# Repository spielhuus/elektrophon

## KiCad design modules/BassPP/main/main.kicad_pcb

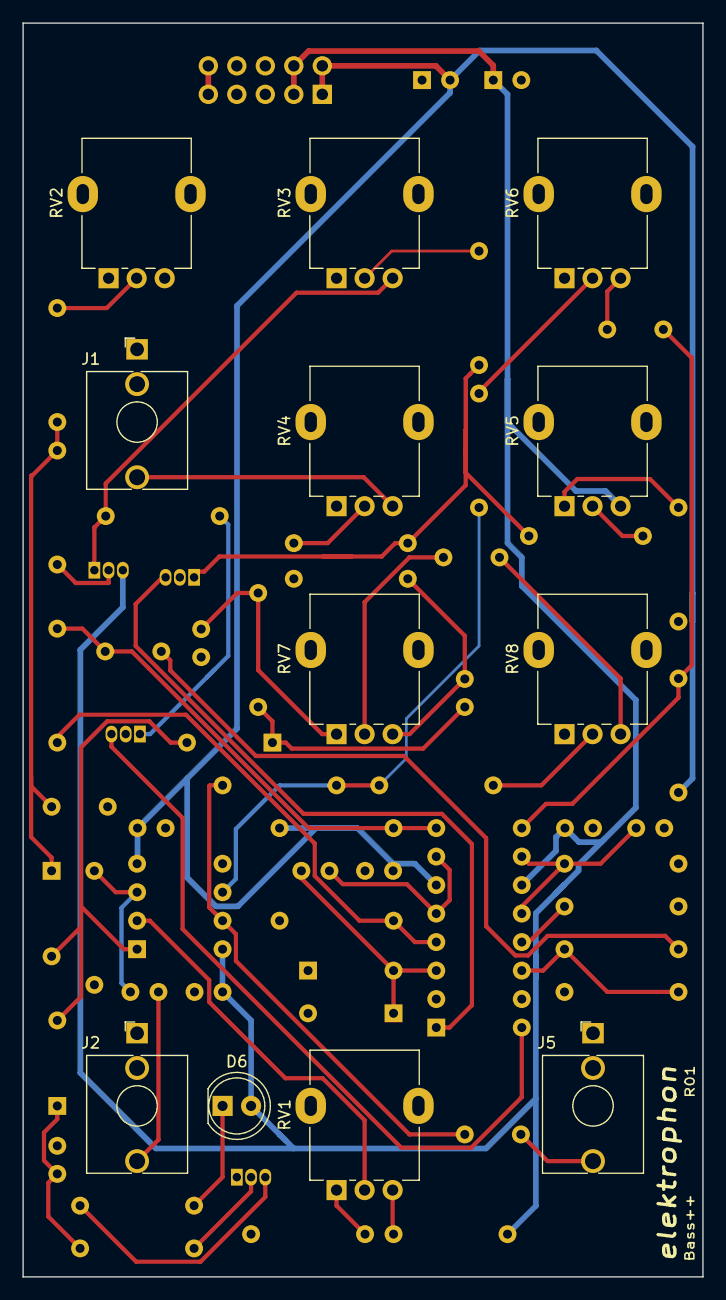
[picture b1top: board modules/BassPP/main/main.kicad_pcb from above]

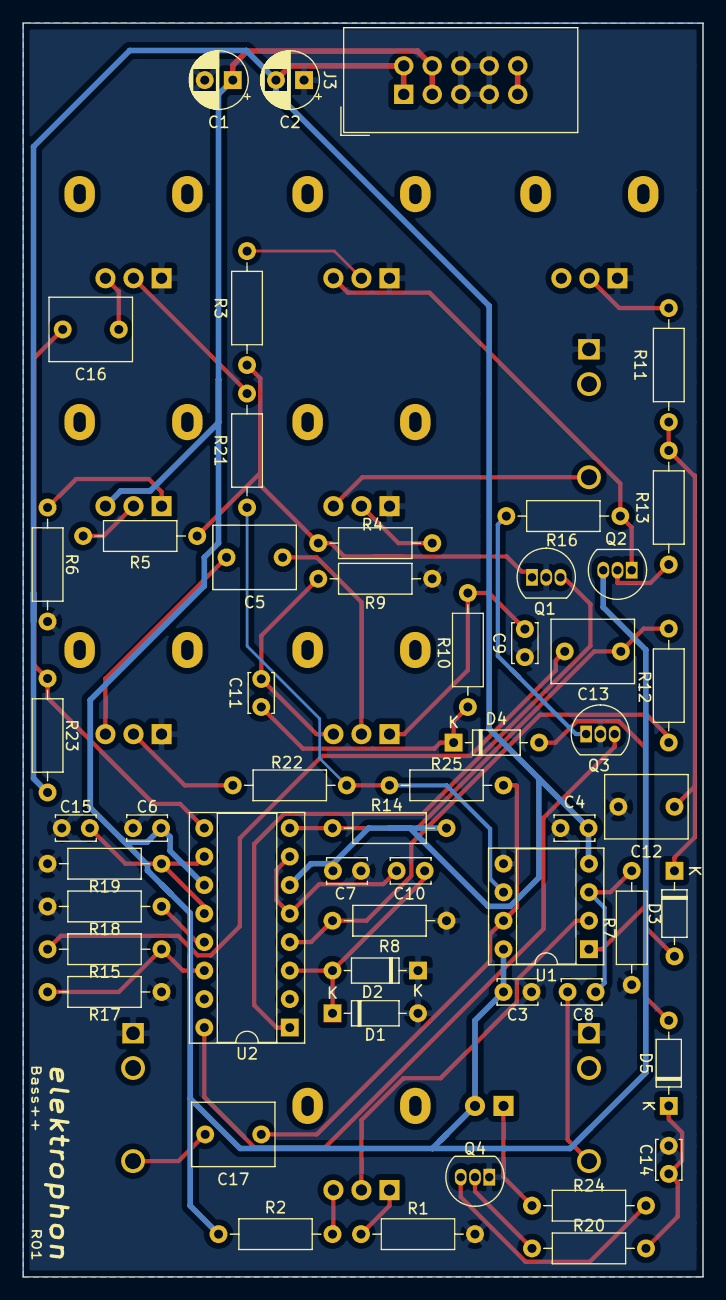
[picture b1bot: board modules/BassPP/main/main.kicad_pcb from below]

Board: 2 copper layers, 60.6 x 111.8 mm, 66 parts (54 on the bottom side), 47 nets.

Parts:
C1, C2: 10u; CP_Radial_D5.0mm_P2.50mm
C3, C4, C6, C7, C9, C11: 0.1u; C_Disc_D3.4mm_W2.1mm_P2.50mm
C5, C12, C13, C16, C17: 2u2; C_Rect_L7.2mm_W5.5mm_P5.00mm_FKS2_FKP2_MKS2_MKP2
C8: 1n; C_Disc_D3.4mm_W2.1mm_P2.50mm
C10, C14, C15: 10n; C_Disc_D3.4mm_W2.1mm_P2.50mm
D1, D2, D3, D4, D5: 1N4148; D_DO-35_SOD27_P7.62mm_Horizontal
D6: LED; LED_D5.0mm
J1, J5: CV; Jack_3.5mm_QingPu_WQP-PJ398SM_Vertical_CircularHoles
J2: Trigger; Jack_3.5mm_QingPu_WQP-PJ398SM_Vertical_CircularHoles
J3: IDC Header; IDC-Header_2x05_P2.54mm_Vertical
Q1, Q3: 2N3906; TO-92_Inline
Q2, Q4: 2N3904; TO-92_Inline
R1: 100; R_Axial_DIN0207_L6.3mm_D2.5mm_P10.16mm_Horizontal
R2, R12, R16: 20k; R_Axial_DIN0207_L6.3mm_D2.5mm_P10.16mm_Horizontal
R3, R15, R21, R22, R25: 100k; R_Axial_DIN0207_L6.3mm_D2.5mm_P10.16mm_Horizontal
R4, R19: 56k; R_Axial_DIN0207_L6.3mm_D2.5mm_P10.16mm_Horizontal
R5: 27k; R_Axial_DIN0207_L6.3mm_D2.5mm_P10.16mm_Horizontal
R6: 3k3; R_Axial_DIN0207_L6.3mm_D2.5mm_P10.16mm_Horizontal
R7: 1M; R_Axial_DIN0207_L6.3mm_D2.5mm_P10.16mm_Horizontal
R8, R9: 2k; R_Axial_DIN0207_L6.3mm_D2.5mm_P10.16mm_Horizontal
R10, R13, R23: 10k; R_Axial_DIN0207_L6.3mm_D2.5mm_P10.16mm_Horizontal
R11: 1k; R_Axial_DIN0207_L6.3mm_D2.5mm_P10.16mm_Horizontal
R14: 5k1; R_Axial_DIN0207_L6.3mm_D2.5mm_P10.16mm_Horizontal
R17, R18: 220; R_Axial_DIN0207_L6.3mm_D2.5mm_P10.16mm_Horizontal
R20: 220k; R_Axial_DIN0207_L6.3mm_D2.5mm_P10.16mm_Horizontal
R24: 1.5k; R_Axial_DIN0207_L6.3mm_D2.5mm_P10.16mm_Horizontal
RV1, RV3, RV7: 10k; Potentiometer_Alpha_RD901F-40-00D_Single_Vertical
RV2: 500k; Potentiometer_Alpha_RD901F-40-00D_Single_Vertical
RV4, RV5, RV6, RV8: 100k; Potentiometer_Alpha_RD901F-40-00D_Single_Vertical
U1: TL072; DIP-8_W7.62mm_Socket
U2: LM13700; DIP-16_W7.62mm_Socket

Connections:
+5V: J3.9, J3.10
+15V: C1.1, C3.1, C6.1, D6.2, J3.3, J3.4, Q2.3, R2.1, RV5.3, U1.8, U2.11
-15V: C2.2, C4.2, C7.2, J3.1, J3.2, R14.1, R23.1, U1.4, U2.6
/PULSE: D3.2, D4.2, D5.2, U1.1
/Shell: C16.1, RV6.3
GND: C1.2, C2.1, C3.2, C4.1, C6.2, C7.1, C9.1, C12.2, C14.2, C15.1, D1.1, D2.2, J1.S, J2.S, J3.5, J3.6, J3.7, J3.8, J5.S, Q1.2, Q3.2, Q4.1, R1.1, R6.1, R7.1, R8.2, R9.1, R17.1, R18.1, R19.1, RV2.1, RV3.1, RV4.1, RV6.1, RV8.1, U1.5
unnamed: C5.1, RV7.2
unnamed: C5.2, RV8.3
unnamed: C8.1, J2.T
unnamed: C8.2, R7.2, U1.3
unnamed: C9.2, R10.1, RV7.1
unnamed: C10.1, U2.5, U2.7
unnamed: C10.2, D1.2, D2.1, U2.3
unnamed: C11.1, D4.1, R10.2
unnamed: C11.2, R9.2, RV7.3
unnamed: C12.1, D3.1, R11.2, R13.2
unnamed: C13.1, R15.1
unnamed: C13.2, R12.1, R14.2, U2.8
unnamed: C14.1, D5.1, R20.2
unnamed: C15.2, R19.2, U2.10, U2.12
unnamed: C16.2, R23.2, U2.9
unnamed: C17.1, R25.1, U1.7
unnamed: C17.2, J5.T
unnamed: D6.1, R24.1
unnamed: J1.T, RV4.3
unnamed: Q1.1, R3.1, R4.1, R5.1
unnamed: Q1.3, U2.1
unnamed: Q2.1, R16.2, RV3.3
unnamed: Q2.2, R13.1
unnamed: Q3.1, R16.1
unnamed: Q3.3, U2.16
unnamed: Q4.2, R20.1
unnamed: Q4.3, R24.2
unnamed: R1.2, RV1.1
unnamed: R2.2, RV1.3
unnamed: R3.2, RV3.2
unnamed: R4.2, RV4.2
unnamed: R5.2, RV5.2
unnamed: R6.2, RV5.1
unnamed: R11.1, RV2.2
unnamed: R8.1, R12.2, U2.4
unnamed: R15.2, R17.2, U2.14
unnamed: R18.2, U2.13
unnamed: R21.1, R22.1, R25.2, U1.6
unnamed: R21.2, RV6.2
unnamed: R22.2, RV8.2
unnamed: RV1.2, U1.2

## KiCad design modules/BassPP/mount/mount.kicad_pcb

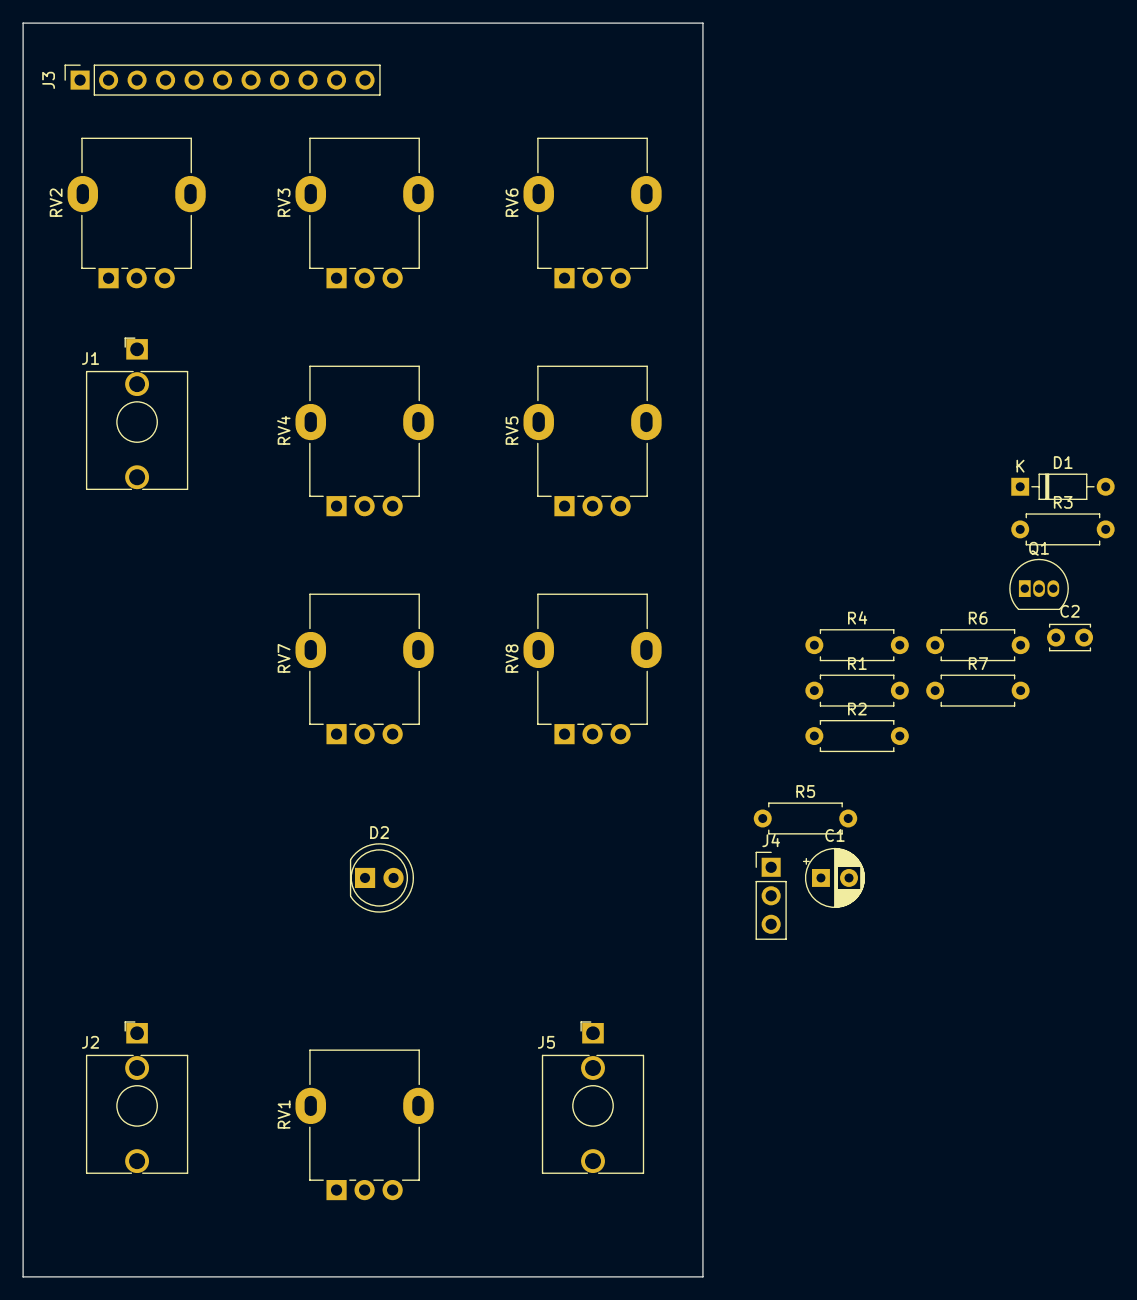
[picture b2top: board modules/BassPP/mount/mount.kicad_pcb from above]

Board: 2 copper layers, 60.6 x 111.8 mm, 25 parts (0 on the bottom side), 21 nets, no tracks yet.

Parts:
C1: 2u2; CP_Radial_D5.0mm_P2.50mm
C2: 10n; C_Disc_D3.4mm_W2.1mm_P2.50mm
D1: 1N4148; D_DO-35_SOD27_P7.62mm_Horizontal
D2: LED; LED_D5.0mm_FlatTop
J1, J2, J5: AudioJack3_Ground; Jack_3.5mm_QingPu_WQP-PJ398SM_Vertical_CircularHoles
J3: Pin Header; PinSocket_1x11_P2.54mm_Vertical
J4: Pin Header; PinHeader_1x03_P2.54mm_Vertical
Q1: 2N3904; TO-92_Inline
R1: 100; R_Axial_DIN0207_L6.3mm_D2.5mm_P7.62mm_Horizontal
R2: 20k; R_Axial_DIN0207_L6.3mm_D2.5mm_P7.62mm_Horizontal
R3: 100k; R_Axial_DIN0207_L6.3mm_D2.5mm_P7.62mm_Horizontal
R4: 56k; R_Axial_DIN0207_L6.3mm_D2.5mm_P7.62mm_Horizontal
R5: 27k; R_Axial_DIN0207_L6.3mm_D2.5mm_P7.62mm_Horizontal
R6: 3k3; R_Axial_DIN0207_L6.3mm_D2.5mm_P7.62mm_Horizontal
R7: 220k; R_Axial_DIN0207_L6.3mm_D2.5mm_P7.62mm_Horizontal
RV1, RV3, RV8: 10k; Potentiometer_Alpha_RD901F-40-00D_Single_Vertical
RV2: 500k; Potentiometer_Alpha_RD901F-40-00D_Single_Vertical
RV4, RV5, RV6, RV7: 100k; Potentiometer_Alpha_RD901F-40-00D_Single_Vertical

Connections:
+15V: D2.2, J4.1, R2.1, RV5.1
/ImpactVolume1: J3.6, RV7.1
/ImpactVolume2: J3.8, RV7.3
/OUT: J3.10, J5.T
/SENSITIVITY: J3.4, RV1.2
/Shell: J3.7, RV6.1
/TRIGGER: J2.T, J3.5
GND: C2.2, J1.S, J2.S, J4.2, J5.S, Q1.1, R1.1, R6.1, RV2.3, RV3.3, RV4.3, RV6.3, RV8.3
unnamed: C1.1, RV8.1
unnamed: C1.2, RV7.2
unnamed: C2.1, D1.1, R7.2
unnamed: D2.1, Q1.3
unnamed: J1.T, RV4.1
unnamed: Q1.2, R7.1
unnamed: R1.2, RV1.1
unnamed: R2.2, RV1.3
unnamed: R3.1, R4.1, R5.1
unnamed: R3.2, RV3.2
unnamed: R4.2, RV4.2
unnamed: R5.2, RV5.2
unnamed: R6.2, RV5.3

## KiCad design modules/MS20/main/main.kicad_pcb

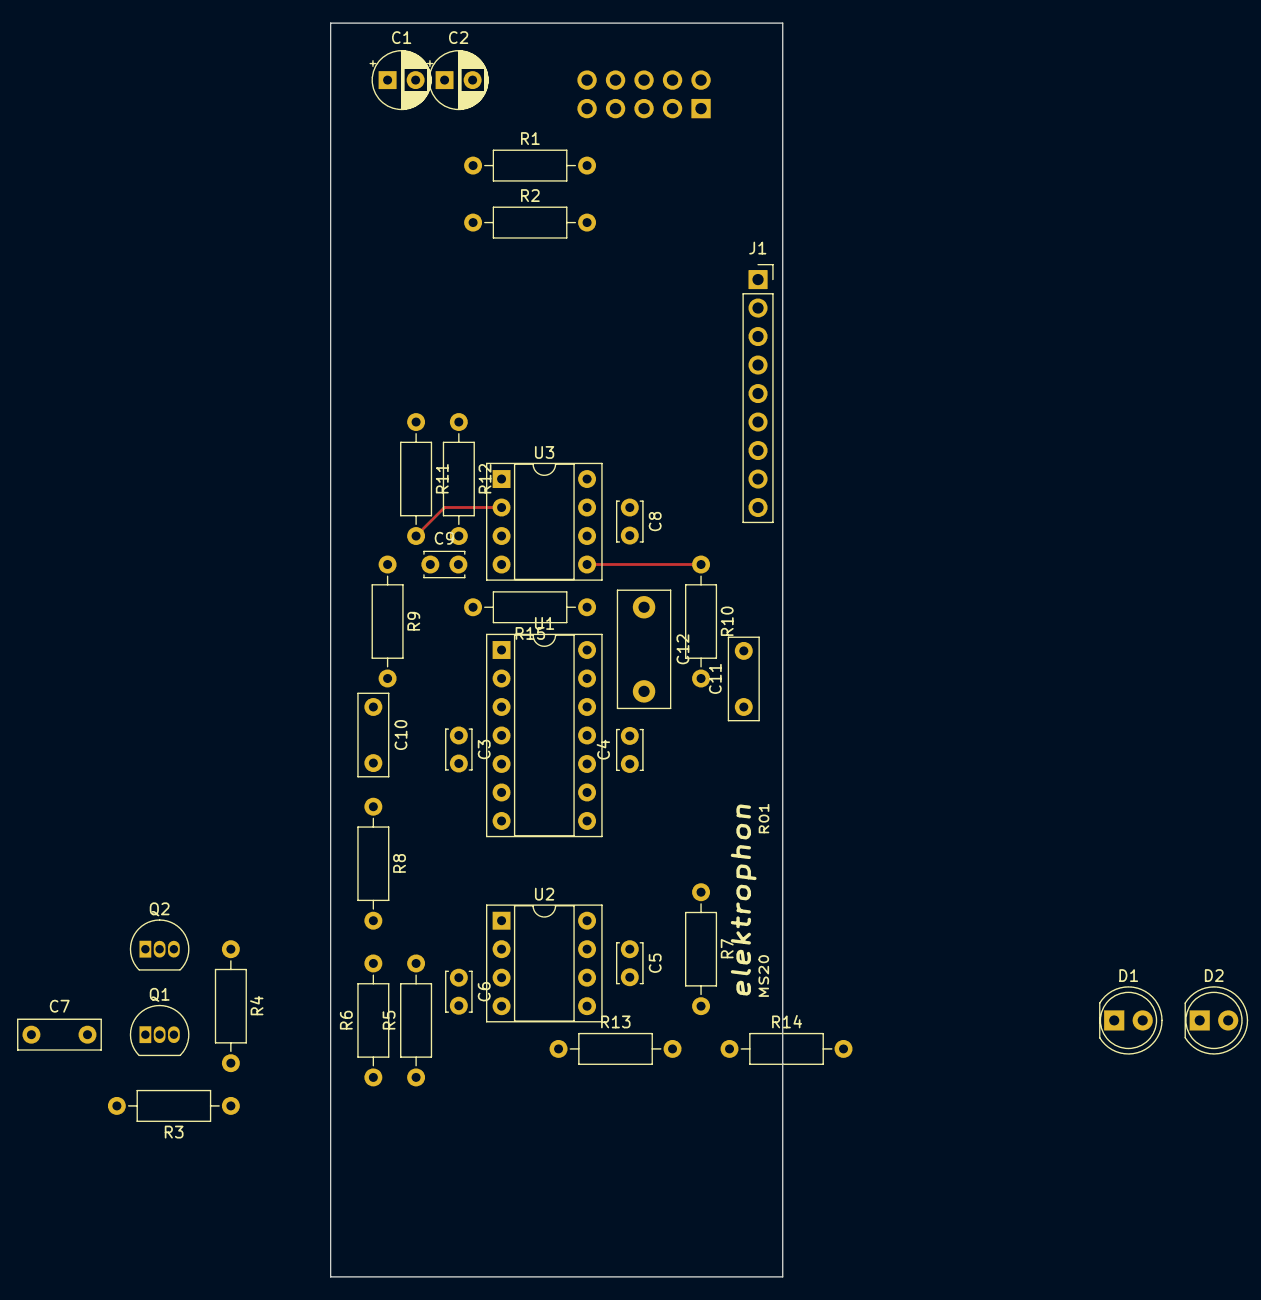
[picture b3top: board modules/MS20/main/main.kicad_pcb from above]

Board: 2 copper layers, 40.3 x 111.8 mm, 36 parts (1 on the bottom side), 23 nets.

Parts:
C1, C2: 22u; CP_Radial_D5.0mm_P2.50mm
C3, C4, C5, C6, C8, C9: 0.1u; C_Disc_D3.4mm_W2.1mm_P2.50mm
C7: 4700p; C_Rect_L7.2mm_W2.5mm_P5.00mm_FKS2_FKP2_MKS2_MKP2
C10, C11: 1n; C_Rect_L7.2mm_W2.5mm_P5.00mm_FKS2_FKP2_MKS2_MKP2
C12: 0.47u; C_Rect_L10.3mm_W4.5mm_P7.50mm_MKS4
D1, D2: LED; LED_D5.0mm
J1: Conn_01x09_Female; PinSocket_1x09_P2.54mm_Vertical
J2: POWER; IDC-Header_2x05_P2.54mm_Vertical
Q1, Q2: BC558; TO-92_Inline
R1, R2: 10; R_Axial_DIN0207_L6.3mm_D2.5mm_P10.16mm_Horizontal
R3: 470k; R_Axial_DIN0207_L6.3mm_D2.5mm_P10.16mm_Horizontal
R4: 4k7; R_Axial_DIN0207_L6.3mm_D2.5mm_P10.16mm_Horizontal
R5, R6, R11, R12: 220; R_Axial_DIN0207_L6.3mm_D2.5mm_P10.16mm_Horizontal
R7, R8, R9, R10, R13, R15: 10k; R_Axial_DIN0207_L6.3mm_D2.5mm_P10.16mm_Horizontal
R14: 1k8; R_Axial_DIN0207_L6.3mm_D2.5mm_P10.16mm_Horizontal
U1: TL074; DIP-14_W7.62mm_Socket
U2, U3: CA3080; DIP-8_W7.62mm_Socket

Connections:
+5V: J2.9, J2.10
+15V: C1.1, C3.1, C5.1, C8.1, J1.1, J2.3, J2.4, R1.1, R1.2, U1.4, U2.7, U3.7
-15V: C2.2, C4.2, C6.2, C9.2, J1.2, J2.1, J2.2, R2.1, R2.2, R3.1, U1.11, U2.4, U3.4
/CV: J1.4, Q1.2, Q2.1, R7.1, R10.2
/HP_IN: C11.2, J1.6
/LP_IN: J1.5, R5.2, R8.2, U2.2
/OUT: C12.2, J1.7, J1.9
/RES2: J1.8, U1.10
GND: C1.2, C2.1, C3.2, C4.1, C5.2, C6.1, C8.2, C9.1, J1.3, J2.5, J2.6, J2.7, J2.8, Q2.2, R5.1, R6.1, R11.1, R12.1, R14.1, U1.5
unnamed: C7.1, R4.2, U1.7
unnamed: C7.2, Q1.1, R3.2, U1.6
unnamed: C10.1, U1.3, U2.6
unnamed: C10.2, D1.1, D2.2, R13.1, U1.8
unnamed: C11.1, U1.12, U3.6
unnamed: C12.1, R15.1, U1.13, U1.14
unnamed: D1.2, D2.1, R13.2, R14.2, U1.9
unnamed: Q1.3, Q2.3, R4.1
unnamed: R6.2, U2.3
unnamed: R7.2, U2.5
unnamed: R8.1, R9.2, U1.1, U1.2
unnamed: R10.1, U3.5
unnamed: R11.2, R15.2, U3.2
unnamed: R9.1, R12.2, U3.3

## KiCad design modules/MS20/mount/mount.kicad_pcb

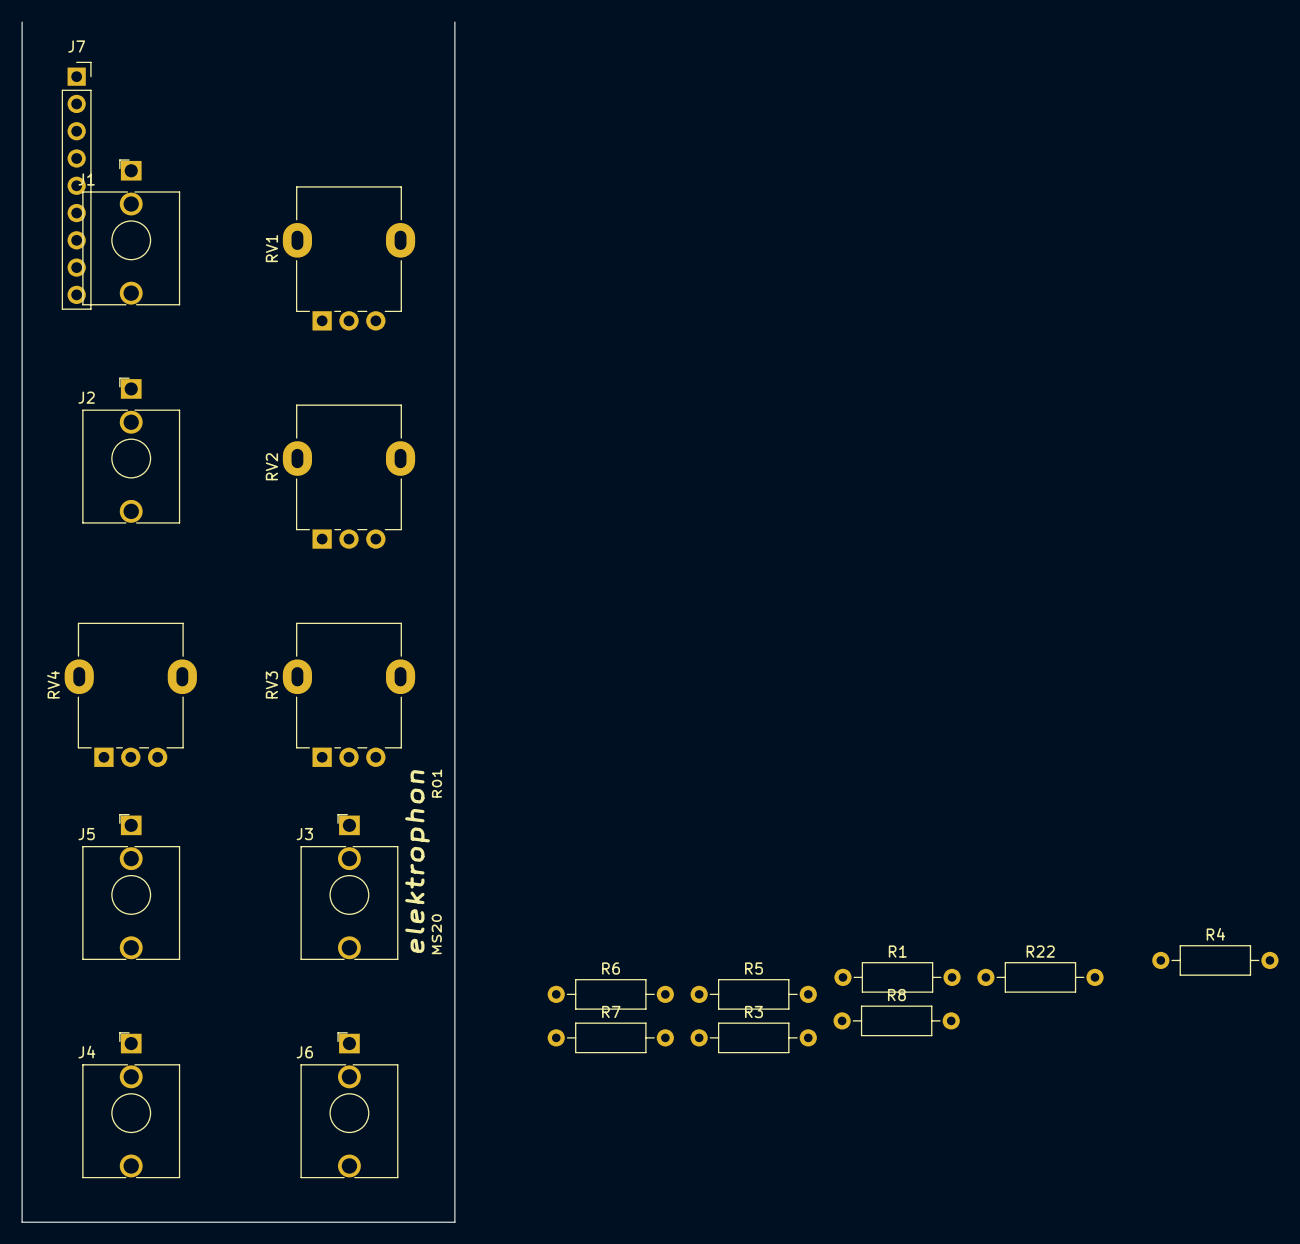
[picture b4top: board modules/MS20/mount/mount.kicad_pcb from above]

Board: 2 copper layers, 40.3 x 111.8 mm, 19 parts (0 on the bottom side), 18 nets, no tracks yet.

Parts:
J1, J2: CV1; Jack_3.5mm_WQP-PJ398SM_Vertical
J3: PITCH; Jack_3.5mm_WQP-PJ398SM_Vertical
J4: LP IN; Jack_3.5mm_WQP-PJ398SM_Vertical
J5: HP IN; Jack_3.5mm_WQP-PJ398SM_Vertical
J6: OUT; Jack_3.5mm_WQP-PJ398SM_Vertical
J7: Conn_01x09_Male; PinSocket_1x09_P2.54mm_Vertical
R1, R7: 10k; R_Axial_DIN0207_L6.3mm_D2.5mm_P10.16mm_Horizontal
R3, R4, R5, R6: 100k; R_Axial_DIN0207_L6.3mm_D2.5mm_P10.16mm_Horizontal
R8: 1k8; R_Axial_DIN0207_L6.3mm_D2.5mm_P10.16mm_Horizontal
R22: 1k; R_Axial_DIN0207_L6.3mm_D2.5mm_P10.16mm_Horizontal
RV1, RV2, RV3: 47k; Potentiometer_Alpha_RD901F-40-00D_Single_Vertical
RV4: 100k; Potentiometer_Alpha_RD901F-40-00D_Single_Vertical

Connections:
+15V: J7.1, RV3.1
-15V: J7.2, RV3.3
/CV: J7.4, R3.1, R4.1, R5.1, R6.1, R8.2
/HP_IN: J7.6, R1.1
/LP_IN: J7.5, R7.1
/OUT: J7.9, R22.1
/RES1: J7.7, RV4.1
/RES2: J7.8, RV4.2
GND: J1.S, J2.S, J3.S, J4.S, J5.S, J5.TN, J6.S, J7.3, R8.1, RV1.1, RV2.1, RV4.3
unnamed: J1.T, RV1.3
unnamed: J2.T, RV2.3
unnamed: J3.T, R5.2
unnamed: J4.T, R7.2
unnamed: J5.T, R1.2
unnamed: J6.T, R22.2
unnamed: R3.2, RV1.2
unnamed: R4.2, RV2.2
unnamed: R6.2, RV3.2

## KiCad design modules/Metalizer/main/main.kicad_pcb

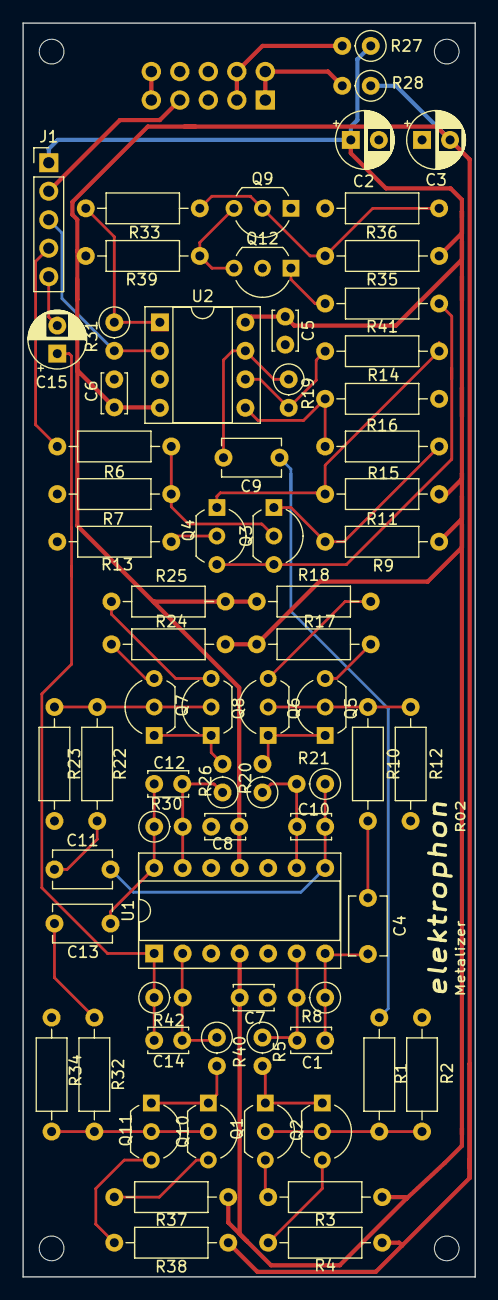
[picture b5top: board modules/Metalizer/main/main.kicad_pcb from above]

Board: 2 copper layers, 40.3 x 111.8 mm, 76 parts (1 on the bottom side), 49 nets.

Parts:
C1, C10, C12, C14: 27p; C_Disc_D3.4mm_W2.1mm_P2.50mm
C2, C3, C15: 10u; CP_Radial_D5.0mm_P2.50mm
C4, C9, C11, C13: 680n; C_Disc_D5.1mm_W3.2mm_P5.00mm
C5, C6, C7, C8: 0.1u; C_Disc_D3.4mm_W2.1mm_P2.50mm
H1, H2, H3, H4: MountingHole; MountingHole_2.2mm_M2
J1: Conn_01x05_Female; PinHeader_1x05_P2.54mm_Vertical
J2: POWER; IDC-Header_2x05_P2.54mm_Vertical
Q1, Q5, Q7, Q10: BC559; TO-92_Inline_Wide
Q2, Q6, Q8, Q11: BC549; TO-92_Inline_Wide
Q3, Q4, Q9, Q12: BC547; TO-92_Inline_Wide
R1, R10, R22, R32: 27k; R_Axial_DIN0207_L6.3mm_D2.5mm_P10.16mm_Horizontal
R2, R12, R23, R34: 68k; R_Axial_DIN0207_L6.3mm_D2.5mm_P10.16mm_Horizontal
R3, R4, R17, R18, R24, R25, R37, R38: 22k; R_Axial_DIN0207_L6.3mm_D2.5mm_P10.16mm_Horizontal
R5, R20, R26, R40: 10k; R_Axial_DIN0207_L6.3mm_D2.5mm_P2.54mm_Vertical
R6, R35: 120k; R_Axial_DIN0207_L6.3mm_D2.5mm_P10.16mm_Horizontal
R7: 820; R_Axial_DIN0207_L6.3mm_D2.5mm_P10.16mm_Horizontal
R8, R21, R30, R42: 120k; R_Axial_DIN0207_L6.3mm_D2.5mm_P2.54mm_Vertical
R9, R11, R14, R15: 15k; R_Axial_DIN0207_L6.3mm_D2.5mm_P10.16mm_Horizontal
R13: 1k; R_Axial_DIN0207_L6.3mm_D2.5mm_P10.16mm_Horizontal
R16: 150k; R_Axial_DIN0207_L6.3mm_D2.5mm_P10.16mm_Horizontal
R19, R31: 150k; R_Axial_DIN0207_L6.3mm_D2.5mm_P2.54mm_Vertical
R27, R28: 10; R_Axial_DIN0207_L6.3mm_D2.5mm_P2.54mm_Vertical
R33: 100k; R_Axial_DIN0207_L6.3mm_D2.5mm_P10.16mm_Horizontal
R36: 1k5; R_Axial_DIN0207_L6.3mm_D2.5mm_P10.16mm_Horizontal
R39: 18k; R_Axial_DIN0207_L6.3mm_D2.5mm_P10.16mm_Horizontal
R41: 10; R_Axial_DIN0207_L6.3mm_D2.5mm_P10.16mm_Horizontal
U1: TL074; DIP-14_W7.62mm_Socket
U2: TL072; DIP-8_W7.62mm_Socket

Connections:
+5V: J2.9, J2.10
+15V: C2.1, C5.1, C7.1, J1.1, R3.2, R9.2, R11.2, R17.2, R24.2, R27.1, R35.2, R37.2, U1.4, U2.8
-15V: C3.2, C6.2, C8.2, R4.1, R18.1, R25.1, R28.1, R38.1, R39.1, U1.11, U2.4
/CV1: J1.3, R31.2, U2.2
/CV2: Q3.3, Q4.3, R41.2
/IN: J1.4, R6.2
/INPUT: C9.1, R1.2
/OUT: C15.2, J1.5
GND: C2.2, C3.1, C5.2, C6.1, C7.2, C8.1, J1.2, J2.5, J2.6, J2.7, J2.8, Q9.1, Q12.2, R2.2, R7.1, R12.2, R13.1, R16.1, R23.2, R34.2, R36.1, U1.3, U1.5, U1.10, U1.12, U2.3
unnamed: C1.1, C4.2, R8.1, U1.7
unnamed: C1.2, R5.1, R8.2, U1.6
unnamed: C4.1, R10.2
unnamed: C9.2, R19.1, U2.7
unnamed: C10.1, C11.2, R21.1, U1.8
unnamed: C10.2, R20.1, R21.2, U1.9
unnamed: C11.1, R22.2
unnamed: C12.1, C13.2, R30.1, U1.14
unnamed: C12.2, R26.1, R30.2, U1.13
unnamed: C13.1, R32.2
unnamed: C14.1, C15.1, R42.1, U1.1
unnamed: C14.2, R40.1, R42.2, U1.2
unnamed: Q1.1, Q2.1, R5.2
unnamed: Q1.2, Q2.2, R1.1, R2.1
unnamed: Q1.3, R3.1
unnamed: Q2.3, R4.2
unnamed: Q3.1, R9.1, R15.2
unnamed: Q3.2, R6.1, R7.2
unnamed: Q4.1, R11.1, R14.2
unnamed: Q4.2, R13.2
unnamed: Q5.1, Q6.1, R20.2
unnamed: Q5.2, Q6.2, R10.1, R12.1
unnamed: Q5.3, R17.1
unnamed: Q6.3, R18.2
unnamed: Q7.1, Q8.1, R26.2
unnamed: Q7.2, Q8.2, R22.1, R23.1
unnamed: Q7.3, R24.1
unnamed: Q8.3, R25.2
unnamed: Q9.2, R33.1, R35.1, R36.2
unnamed: Q10.1, Q11.1, R40.2
unnamed: Q10.2, Q11.2, R32.1, R34.1
unnamed: Q10.3, R37.1
unnamed: Q11.3, R38.2
unnamed: Q12.1, R41.1
unnamed: Q9.3, Q12.3, R39.2
unnamed: R14.1, R19.2, U2.6
unnamed: R15.1, R16.2, U2.5
unnamed: R31.1, R33.2, U2.1
PWR_+15V: J2.3, J2.4, R27.2
PWR_-15V: J2.1, J2.2, R28.2

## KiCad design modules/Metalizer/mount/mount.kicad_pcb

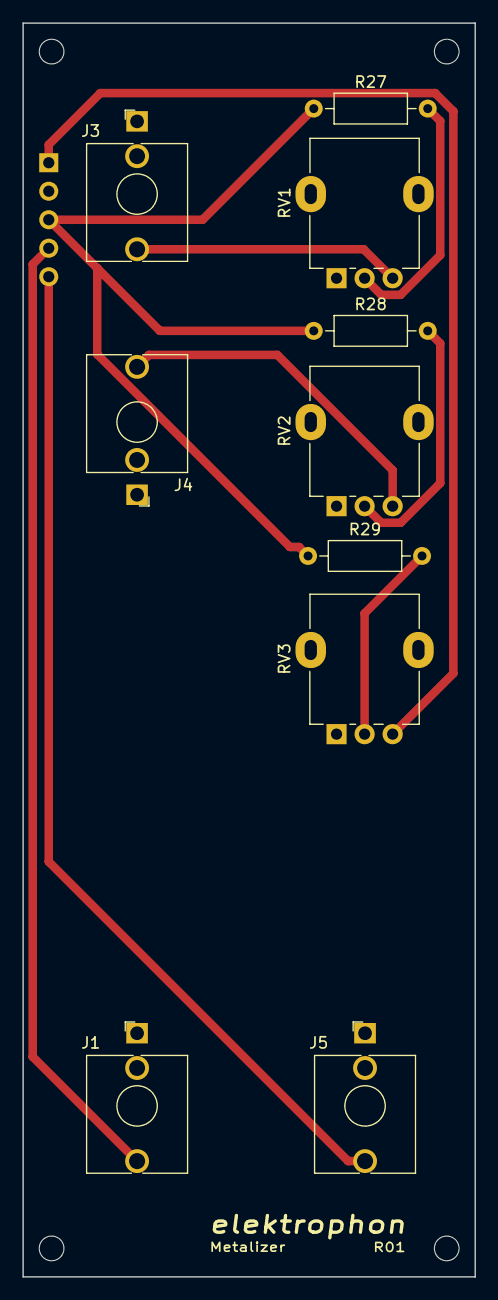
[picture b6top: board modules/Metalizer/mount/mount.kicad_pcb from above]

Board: 2 copper layers, 40.3 x 111.8 mm, 15 parts (1 on the bottom side), 10 nets.

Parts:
H1, H2, H3, H4: MountingHole; MountingHole_2.2mm_M2
J1: INPUT; Jack_3.5mm_WQP-PJ398SM_Vertical
J2: Conn_01x05_Male; PinHeader_1x05_P2.54mm_Vertical
J3: CV1; Jack_3.5mm_WQP-PJ398SM_Vertical
J4: CV2; Jack_3.5mm_WQP-PJ398SM_Vertical
J5: OUT; Jack_3.5mm_WQP-PJ398SM_Vertical
R27, R28, R29: 270k; R_Axial_DIN0207_L6.3mm_D2.5mm_P10.16mm_Horizontal
RV1, RV2, RV3: 100k; Potentiometer_Alpha_RD901F-40-00D_Single_Vertical

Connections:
+15V: J2.1, RV3.3
/CV: J2.3, R27.1, R28.1, R29.1
/IN: J1.T, J2.4
/OUT: J2.5, J5.T
GND: J1.S, J2.2, J3.S, J4.S, J5.S, RV1.1, RV2.1, RV3.1
unnamed: J3.T, RV1.3
unnamed: J4.T, RV2.3
unnamed: R27.2, RV1.2
unnamed: R28.2, RV2.2
unnamed: R29.2, RV3.2

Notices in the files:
modules/BassPP/main/main.kicad_pcb:
License CC BY 4.0 - Attribution 4.0 International
